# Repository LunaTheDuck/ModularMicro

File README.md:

# ModularMicro
A Bunch of modules that can be used to make a microcontroller  
None of the module have been tested yet  
Inspired from ben eater's [8bit microcontroller serie](https://youtube.com/playlist?list=PLowKtXNTBypGqImE405J2565dvjafglHU)
# TODO
Design PCB

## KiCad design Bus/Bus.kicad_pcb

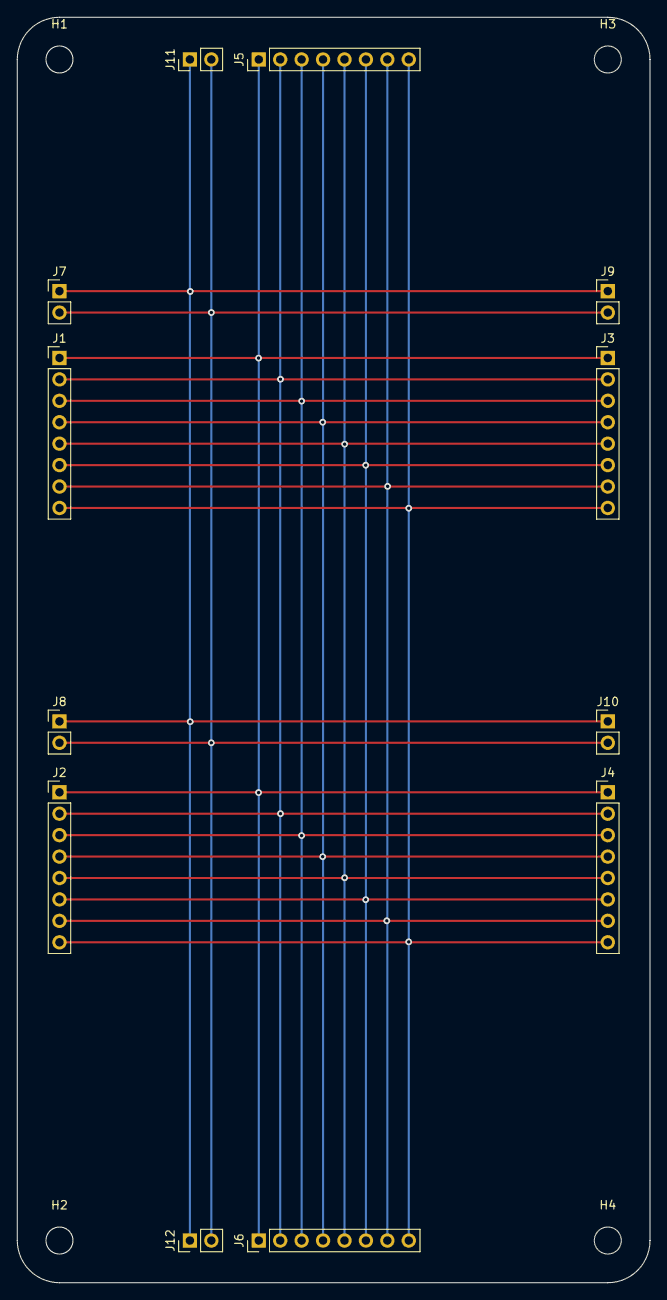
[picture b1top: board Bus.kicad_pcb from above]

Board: 2 copper layers, 75.0 x 150.0 mm, 16 parts (0 on the bottom side), 10 nets.

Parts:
H1, H2, H3, H4: MountingHole; MountingHole_3.2mm_M3
J1, J2, J3, J4, J5, J6: Conn_01x08; PinHeader_1x08_P2.54mm_Vertical
J7, J8, J9, J10, J11, J12: Conn_01x02; PinHeader_1x02_P2.54mm_Vertical

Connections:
unnamed: J1.1, J2.1, J3.1, J4.1, J5.1, J6.1
unnamed: J1.2, J2.2, J3.2, J4.2, J5.2, J6.2
unnamed: J1.3, J2.3, J3.3, J4.3, J5.3, J6.3
unnamed: J1.4, J2.4, J3.4, J4.4, J5.4, J6.4
unnamed: J1.5, J2.5, J3.5, J4.5, J5.5, J6.5
unnamed: J1.6, J2.6, J3.6, J4.6, J5.6, J6.6
unnamed: J1.7, J2.7, J3.7, J4.7, J5.7, J6.7
unnamed: J1.8, J2.8, J3.8, J4.8, J5.8, J6.8
unnamed: J7.1, J8.1, J9.1, J10.1, J11.1, J12.1
unnamed: J7.2, J8.2, J9.2, J10.2, J11.2, J12.2

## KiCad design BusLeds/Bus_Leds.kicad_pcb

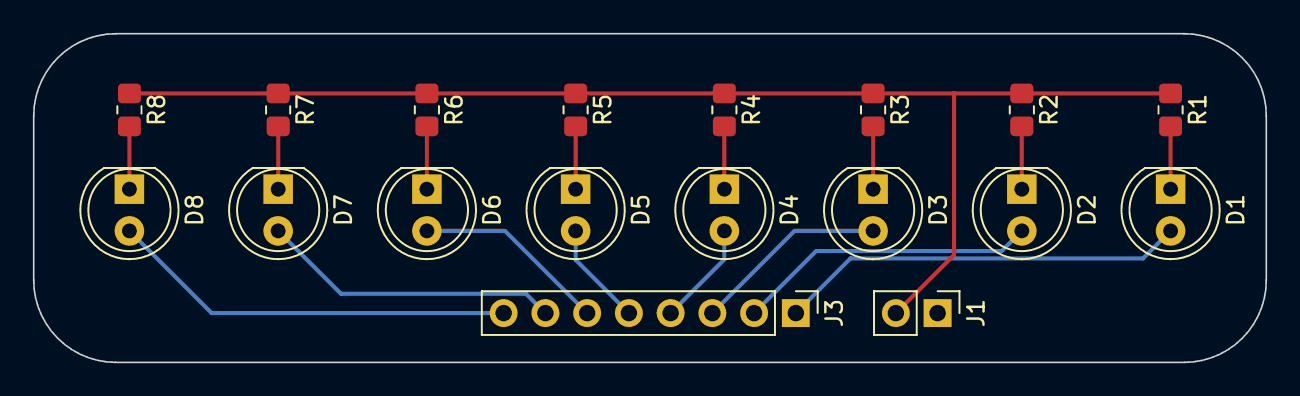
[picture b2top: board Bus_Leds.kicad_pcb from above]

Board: 2 copper layers, 75.0 x 20.0 mm, 18 parts (0 on the bottom side), 17 nets.

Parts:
D1, D2, D3, D4, D5, D6, D7, D8: LED; LED_D5.0mm
J1: Conn_01x02; PinHeader_1x02_P2.54mm_Vertical
J3: Conn_01x08; PinHeader_1x08_P2.54mm_Vertical
R1, R2, R3, R4, R5, R6, R7, R8: 220; R_0805_2012Metric_Pad1.20x1.40mm_HandSolder

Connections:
unnamed: D1.2 (A), J3.1
unnamed: D1.1 (K), R1.2
unnamed: D2.2 (A), J3.2
unnamed: D2.1 (K), R2.2
unnamed: D3.2 (A), J3.3
unnamed: D3.1 (K), R3.2
unnamed: D4.2 (A), J3.4
unnamed: D4.1 (K), R4.2
unnamed: D5.2 (A), J3.5
unnamed: D5.1 (K), R5.2
unnamed: D6.2 (A), J3.6
unnamed: D6.1 (K), R6.2
unnamed: D7.2 (A), J3.7
unnamed: D7.1 (K), R7.2
unnamed: D8.2 (A), J3.8
unnamed: D8.1 (K), R8.2
unnamed: J1.2, R1.1, R2.1, R3.1, R4.1, R5.1, R6.1, R7.1, R8.1

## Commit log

2023-06-04 Added cappacitor to all Schematic
2023-06-06 Started assigning footprint
2023-06-06 Started assigning footprint.
2023-06-10 Updated Footprint
2023-06-19 Added LICENSE
2023-08-31 Made Register 8bit pcb
2023-12-31 Made 8Bit Register PCB
